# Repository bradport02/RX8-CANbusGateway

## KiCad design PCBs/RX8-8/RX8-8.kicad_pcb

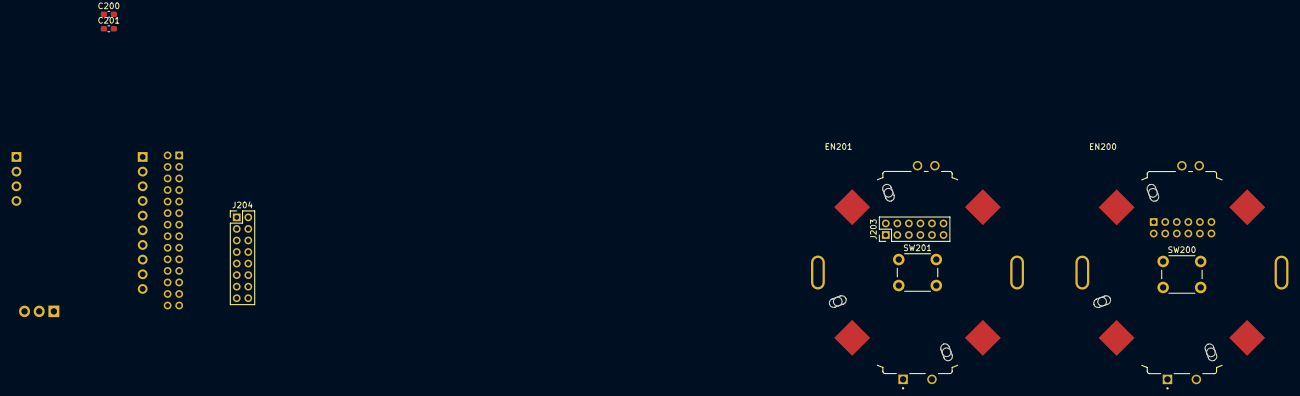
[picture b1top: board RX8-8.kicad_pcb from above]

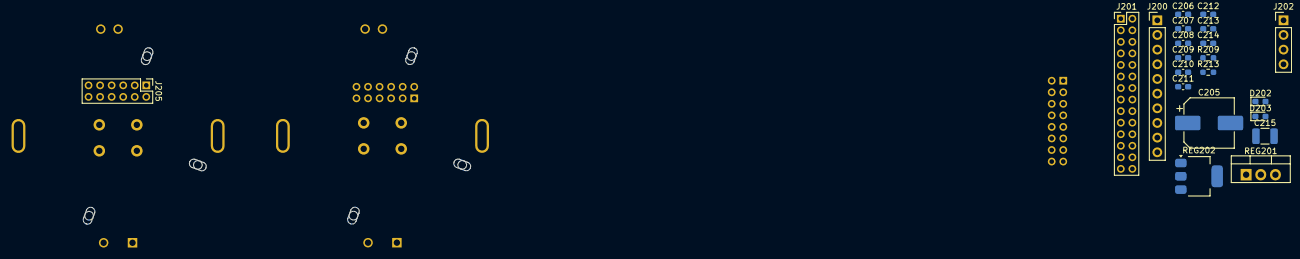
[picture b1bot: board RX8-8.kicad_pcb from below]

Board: 2 copper layers, 29 parts (21 on the bottom side), 30 nets, no tracks yet.

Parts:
C200, C201, C206, C207, C209, C211, C212, C213: 10n; C_0603_1608Metric_Pad1.08x0.95mm_HandSolder
C205: 47u; CP_Elec_8x10.5
C208, C210, C214: 100n; C_0603_1608Metric_Pad1.08x0.95mm_HandSolder
C215: 10u; C_1210_3225Metric_Pad1.33x2.70mm_HandSolder
D202, D203: LED; LED_0603_1608Metric_Pad1.05x0.95mm_HandSolder
EN200, EN201: PER351-P115-N0010; XDCR_PER351-P115-N0010
J200: OUT_TO_CCU; PinHeader_1x10_P2.54mm_Vertical
J201: Conn_01x24_Pin; PinHeader_2x14_P2.00mm_Vertical
J202: IND; PinHeader_1x04_P2.54mm_Vertical
J203, J205: GC9A01; PinHeader_2x06_P2.00mm_Vertical
J204: GC9A01; PinHeader_2x08_P2.00mm_Vertical
R209: 2K2; R_0603_1608Metric_Pad0.98x0.95mm_HandSolder
R213: 22k; R_0603_1608Metric_Pad0.98x0.95mm_HandSolder
REG201: LM7805_TO220; TO-220-3_Vertical
REG202: LD1117S33TR_SOT223; SOT-223-3_TabPin2
SW200, SW201: SW_Push; SW_PUSH_6mm_H4.3mm

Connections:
+12V: C205.1, C208.1, J201.1, REG201.1 (VI)
/Power and IO/CS1: J201.19, J203.8
/Power and IO/CS2: J201.22, J204.6
/Power and IO/CS3: J201.21, J205.8
/Power and IO/EN1A: C206.1, EN200.A, J201.5
/Power and IO/EN1B: C207.1, EN200.B, J201.6
/Power and IO/EN1C: C209.1, EN200.C, J201.7
/Power and IO/EN2A: C211.1, EN201.A, J201.8
/Power and IO/EN2B: C212.1, EN201.B, J201.9
/Power and IO/EN2C: C213.1, EN201.C, J201.10
/Power and IO/LCD_BACK: J201.27, J202.4, J203.2, J204.2, J205.2
/Power and IO/LCD_DC: J201.23, J203.7, J204.5, J205.7
/Power and IO/LCD_RST1: J201.14, J203.11
/Power and IO/LCD_RST2: J201.15, J204.9
/Power and IO/LCD_RST3: J201.24, J205.11
/Power and IO/MOSI: J201.18, J203.10, J204.8, J205.10
/Power and IO/SCK: J203.9, J204.7, J205.9
/Power and IO/SCL: J201.4, J204.14
/Power and IO/SDA: J201.3, J204.15
/Power and IO/SW1: C200.1, J201.11, SW200.1
/Power and IO/SW2: C201.1, J201.12, SW201.1
/Power and IO/TP_INT: J201.17, J204.13
/Power and IO/TP_RST: J201.16, J204.12
GND: C200.2, C201.2, C205.2, C208.2, C210.2, C211.2, C212.2, C213.2, C214.2, C215.2, EN200.D, EN200.SH1 (SHIELD), EN200.SH2 (SHIELD), EN200.SH3 (SHIELD), EN200.SH4 (SHIELD), EN200.SH5 (SHIELD), EN200.SH6 (SHIELD), EN201.D, EN201.SH1 (SHIELD), EN201.SH2 (SHIELD), EN201.SH3 (SHIELD), EN201.SH4 (SHIELD), EN201.SH5 (SHIELD), EN201.SH6 (SHIELD), R209.1, R213.2, REG201.2 (GND), REG202.1 (GND), SW200.2, SW201.2
unnamed: C206.2, C207.2, C209.2
unnamed: D202.1 (K), R209.2
unnamed: D203.1 (K), R213.1
P3V3: C215.1, D203.2 (A), J205.4, REG202.2 (VO)
P5V: C210.1, C214.1, D202.2 (A), J203.4, J204.4, J204.10, REG201.3 (VO), REG202.3 (VI)
PGND: J201.2, J203.1, J203.5, J203.6, J203.12, J204.1, J204.11, J205.1, J205.5, J205.6, J205.12

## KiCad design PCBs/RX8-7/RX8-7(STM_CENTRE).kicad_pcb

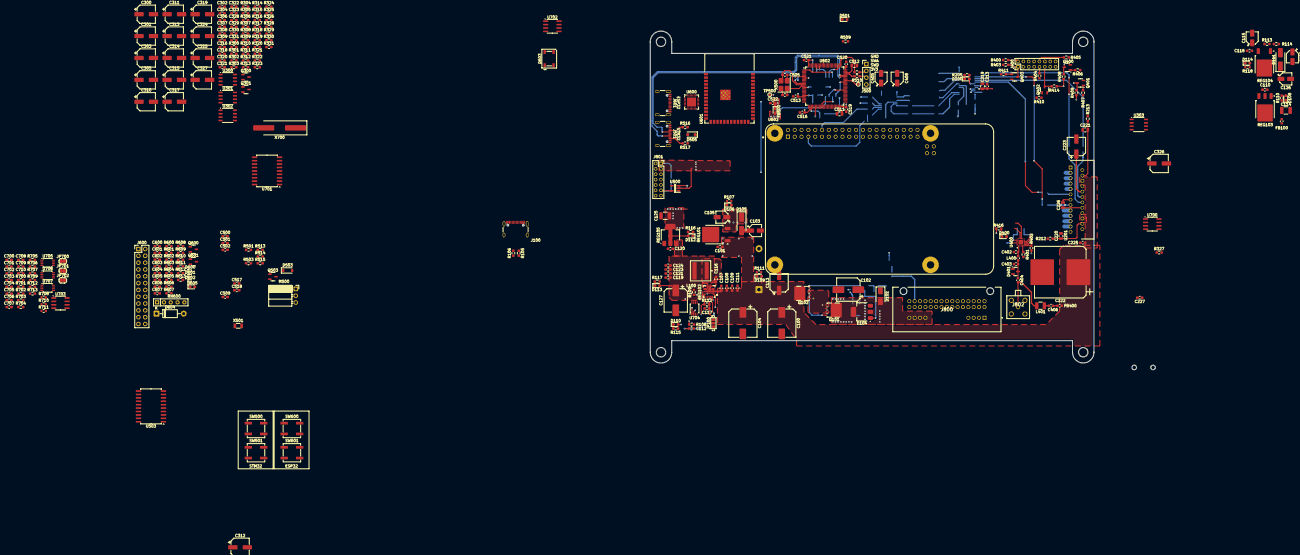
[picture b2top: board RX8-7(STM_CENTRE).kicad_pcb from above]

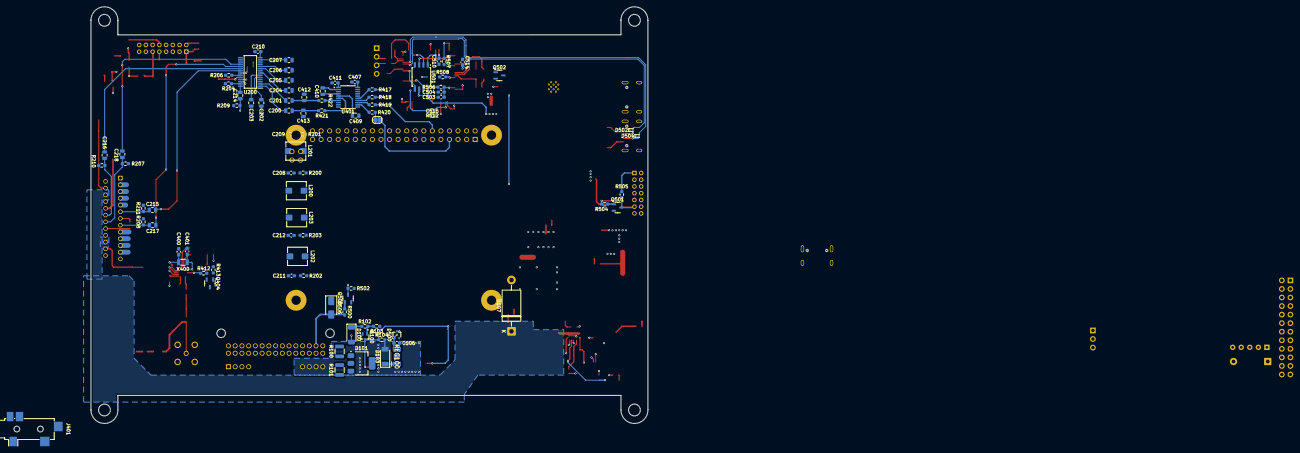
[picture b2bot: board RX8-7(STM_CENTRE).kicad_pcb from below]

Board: 4 copper layers, 165.3 x 123.7 mm, 387 parts (88 on the bottom side), 302 nets.

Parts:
C100: 100u; CP_Elec_10x10
C101, C106, C109, C110, C111, C116, C118, C120, C208, C209, C211, C212, C213, C225, C227, C328, C329, C330, C331, C407, C411, C500, C501, C502, C503, C509, C510, C513, C514, C515, C516, C519, C520, C521, C601, C602, C604, C605, C606, C700, C703, C704, C705, C706, C707, C708, C709, C710: 100n; C_0603_1608Metric_Pad1.08x0.95mm_HandSolder
C102: 10u; CP_Elec_8x10.5
C103, C115, C122, C405, C408: 10u; CP_Elec_4x5.4
C104: 220u; CP_Elec_10x10
C105: 1u; CP_Elec_4x5.7
C107, C108, C504, C522, C607: 10u; C_0603_1608Metric_Pad1.08x0.95mm_HandSolder
C112: 22n; C_0603_1608Metric_Pad1.08x0.95mm_HandSolder
C113, C223: 47u; CP_Elec_6.3x5.9
C114, C125: 10u; C_1210_3225Metric_Pad1.33x2.70mm_HandSolder
C117: 4.7u; C_0603_1608Metric_Pad1.08x0.95mm_HandSolder
C119, C121: 47u; C_0603_1608Metric_Pad1.08x0.95mm_HandSolder
C123: 22u; C_0603_1608Metric_Pad1.08x0.95mm_HandSolder
C124: 22uF; C_0603_1608Metric_Pad1.08x0.95mm_HandSolder
C126: 1u; CP_Elec_4x5.4
C127: 470u; CP_Elec_8x10.5
C200, C201, C202, C203, C204, C205, C206, C207, C214, C220, C221: 1u; C_0805_2012Metric
C210: 470n; C_0603_1608Metric_Pad1.08x0.95mm_HandSolder
C215, C216, C217, C218, C409, C410, C412, C413, C511, C512: 2u2; C_0805_2012Metric
C219: 10u; C_0805_2012Metric
C222: 4700u; CP_Elec_18x22
C226: 470n; C_0805_2012Metric
C300, C301, C303, C305, C314, C315, C317, C319: 10u; CP_Elec_6.3x7.7
C302, C304, C316, C318, C600, C603: 1u; C_0603_1608Metric_Pad1.08x0.95mm_HandSolder
C306, C307, C308, C309, C320, C321, C322, C323: 47p; C_0603_1608Metric_Pad1.08x0.95mm_HandSolder
C310, C311, C312, C313, C324, C325, C326, C327: 220u; CP_Elec_6.3x7.7
C400, C401, C701, C702: 22p; C_0603_1608Metric_Pad1.08x0.95mm_HandSolder
C402, C403: NA; C_0603_1608Metric
C404: 470p; C_0603_1608Metric
C406: 10u; C_0603_1608Metric
C505, C508: 12p; C_0603_1608Metric_Pad1.08x0.95mm_HandSolder
C517, C518: 15p; C_0603_1608Metric_Pad1.08x0.95mm_HandSolder
D100, D103: 1N5402; D_SOD-128
D101, D104: D_Zener; SOT-223-3_TabPin2
D102, D506: SMAJ24A; D_SMA
D105, D111: 1N4007; D_SMA_Handsoldering
D106, D108, D109, D110, D112, D113, D114, D200, D400, D501, D605: LED; LED_0603_1608Metric_Pad1.05x0.95mm_HandSolder
D107: 1.5KExxA; D_DO-201AE_P15.24mm_Horizontal
D401: NUP2105L; SOT-23
D500: BAT54W; SOT-323_SC-70
D502, D504, D600, D601, D602: ESD9B5.0ST5G; D_SOD-923
D503: 1N4001; D_SOD-123
D505: 1N5819; D_SOD-123F
D603: WS2812B; LED_WS2812B_PLCC4_5.0x5.0mm_P3.2mm
D604: 1N5819; D_DO-41_SOD81_P10.16mm_Horizontal
FB100, FB400: FerriteBead; C_0603_1608Metric
FB500: FerriteBead; LED_0603_1608Metric_Pad1.05x0.95mm_HandSolder
J100, J501, J601: USB_C_Receptacle_USB2.0_16P; USB_C_Receptacle_GCT_USB4105-xx-A_16P_TopMnt_Horizontal
J400: Conn_01x15_Pin; PinHeader_2x08_P2.00mm_Vertical
J401: AudioJack3_Ground; Jack_3.5mm_CUI_SJ2-3593D-SMT_Horizontal
J500: Conn_01x04_Pin; PinHeader_1x04_P2.54mm_Vertical
J600: Conn_01x24_Pin; PinHeader_2x12_P2.54mm_Vertical
J800: 34958-0383; 349580383
J801: Conn_01x12_Pin; PinSocket_2x07_P2.00mm_Vertical
J802: 59S10H-400T5-A; 59S10H400T5A
JP100: Jumper_3_Bridged12; SolderJumper-3_P1.3mm_Open_Pad1.0x1.5mm_NumberLabels
JP600: Jumper_2_Open; SolderJumper-2_P1.3mm_Open_RoundedPad1.0x1.5mm
JP700, JP701, JP702: Jumper_2_Bridged; SolderJumper-2_P1.3mm_Open_RoundedPad1.0x1.5mm
L100: 4.7uH; XAL7030472MEC
L200, L201, L202, L203: 10u; L_Bourns_SRP5030T
L400: NA; C_0603_1608Metric
L401: 10u; L_1210_3225Metric
M500: Fan_3pin; PinSocket_1x03_P2.54mm_Horizontal
Q100: NPN; SOT65P210X125-3N
Q101, Q102: SQJ407EP-T1_GE3; PowerPAK-SO-8L_Option-2_VIS
Q300, Q301: NPN; SOT-23-3
Q400, Q401, Q402, Q403, Q404, Q500, Q501, Q502, Q503, Q600, Q601: NPN; SOT-23-3(CORRECTED)
R100, R101: 10k; R_1210_3225Metric
R102, R110, R116, R205, R416, R613: 22k; R_0603_1608Metric_Pad0.98x0.95mm_HandSolder
R103, R104, R206, R207, R208, R210, R211, R213, R330, R331, R400, R401, R402, R403, R404, R405, R408, R409, R413, R414, R417, R418, R419, R420, R500, R501, R502, R503, R504, R505, R508, R509, R514, R600, R601, R609, R610, R702, R707, R709, R712, R713: 10k; R_0603_1608Metric_Pad0.98x0.95mm_HandSolder
R105, R106, R516, R517, R604, R605: 5k1; R_0603_1608Metric_Pad0.98x0.95mm_HandSolder
R107, R111, R118: 22k; R_0603_1608Metric
R108: 62k; R_0603_1608Metric_Pad0.98x0.95mm_HandSolder
R109: 51k; R_0603_1608Metric_Pad0.98x0.95mm_HandSolder
R112, R204, R209: 100k; R_0603_1608Metric_Pad0.98x0.95mm_HandSolder
R113: 240R; R_0603_1608Metric_Pad0.98x0.95mm_HandSolder
R114: 1k5; R_0603_1608Metric_Pad0.98x0.95mm_HandSolder
R115, R117: 2K2; R_0603_1608Metric_Pad0.98x0.95mm_HandSolder
R200, R201, R202, R203: 10R; R_0603_1608Metric_Pad0.98x0.95mm_HandSolder
R212, R603: 47k; R_0603_1608Metric_Pad0.98x0.95mm_HandSolder
R300, R301, R314, R315: 27k; R_0603_1608Metric_Pad0.98x0.95mm_HandSolder
R302, R303, R304, R305, R312, R313, R316, R317, R318, R319, R326, R327: 4K7; R_0603_1608Metric_Pad0.98x0.95mm_HandSolder
R306, R307, R320, R321: 1K; R_0603_1608Metric_Pad0.98x0.95mm_HandSolder
R308, R309, R310, R311, R322, R323, R324, R325: 4R7; R_0603_1608Metric_Pad0.98x0.95mm_HandSolder
R328, R329, R406, R407, R410, R411, R412, R512, R515, R608: 1k; R_0603_1608Metric_Pad0.98x0.95mm_HandSolder
R421, R422: 470R; R_0603_1608Metric_Pad0.98x0.95mm_HandSolder
R506, R507, R606, R607, R611, R612, R700, R703, R704: 0R; R_0603_1608Metric_Pad0.98x0.95mm_HandSolder
R510, R511: 22R; R_0603_1608Metric_Pad0.98x0.95mm_HandSolder
R513: 82k; R_0603_1608Metric_Pad0.98x0.95mm_HandSolder
R602: 22k1; R_0603_1608Metric_Pad0.98x0.95mm_HandSolder
R701, R705, R706: 120R; R_0603_1608Metric_Pad0.98x0.95mm_HandSolder
R708, R710, R711: 10k; R_0603_1608Metric
REG100: TPS7B8233QDGNRQ1; SOP65P490X110-9N
REG101: LF80_TO252; TO-252-2
REG102: MPQ4317GRE-5-AEC1-P; QFN-20_MPQ4317_MNP
REG103: NCV1117DT33T5G; TO-252-3_TabPin2
REG104: NCV317MBDTRKG; TO-252-2
REG105: LD1117S33TR_SOT223; SOT-223-3_TabPin2
RN600: R_Network04; R_Array_SIP5
SW500, SW501, SW600, SW601: SW_Push; SW_SPST_B3SL-1002P
TP500, TP501: TestPoint; TestPoint_Pad_D1.0mm
U200: TDA7719; SOP65P640X120-28N
U201: TDA7388; TO100P465X2910X1977-25P
U300, U301, U302, U303: NJM4556A; SSOP-8_3.9x5.05mm_P1.27mm
U400: SI4703-C19-GM; SI4703C19GM
U401: PCM5102A; TSSOP-20_4.4x6.5mm_P0.65mm
U500: MCP1402T-E_OT; SOT95P270X145-5N
U501: W25Q32JVSS; SOIC-8_5.3x5.3mm_P1.27mm
U502: STM32H750VBTx; LQFP-100_14x14mm_P0.5mm
U503: 74HC245; SOIC-20W_7.5x12.8mm_P1.27mm
U600: CP2102N-Axx-xQFN28; QFN-28-1EP_5x5mm_P0.5mm_EP3.35x3.35mm
U601: ESP32-S3-WROOM-1
U602: Raspberry_Pi_5; MODULE_RASPBERRY_PI_4B_4GB
U700, U702, U703: MCP2551-I-SN; SOIC-8_3.9x4.9mm_P1.27mm
U701: MCP2515-xSO; SOIC-18W_7.5x11.6mm_P1.27mm
U704, U705, U706, U707: LM75B; TSSOP-8_3x3mm_P0.65mm
X400, X501: 32.768K; Crystal_SMD_3215-2Pin_3.2x1.5mm
X500: 25MHz; Crystal_SMD_3225-4Pin_3.2x2.5mm_HandSoldering
X700: 8MHz; Crystal_SMD_HC49-SD_HandSoldering

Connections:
3P3: C408.1, C411.1, D400.2 (A), FB100.1, R402.2, R413.2, U400.10 (VIO), U400.11 (VD), U400.16 (VA), U401.1 (CPVDD), U401.8 (AVDD)
8P5: C110.1, C126.1, C213.1, C219.1, C328.2, C329.2, C330.2, C331.2, D111.1 (K), D114.2 (A), R113.1, REG103.3 (VI), REG104.2 (VOUT), U200.24 (VDD), U300.8 (V+), U301.8 (V+), U302.8 (V+), U303.8 (V+)
+12V: C100.1, C101.1, C104.1, C107.1, C108.1, C109.1, C111.1, C113.1, C115.1, C118.1, C222.1, C225.1, D107.1 (A1), D109.2 (A), D503.1 (K), FB400.1, J400.3, J400.4, J600.1, J600.2, M500.2 (+), Q102.5 (D), R330.2, R331.2, R408.2, R409.2, R414.2, REG101.1 (VI), REG102.3 (VIN), REG102.12 (VIN), REG104.3 (VIN), U201.6 (VCC_1), U201.20 (VCC_2)
+BAT: D102.2 (A2), D103.2 (A), D104.2 (A), J800.5, J800.6, J800.7, J800.8, Q101.5 (D), R104.2
/AMPENABLE: J800.28, Q300.1 (C), R330.1
/ANT_IN: C404.2, J802.1, L401.1
/Audio2/APSTATE: R329.1, U601.18 (IO10)
/Audio3/CDBUS+: R411.1, U601.17 (IO9)
/Audio3/CDEJECT: R410.1, U601.12 (IO8)
/Audio3/CDMUTE: R406.1, U601.6 (IO6)
/Audio3/CD_ENABLE: R407.1, U601.7 (IO7)
/Audio3/FMGPIO1: R412.1, U400.19 (GPIO1)
/Audio3/I2S_BCLK: R419.1, U602.12 (GPIO18/SPI1_~CE0/PCM_CLK/PWM0)
/Audio3/I2S_DOUT: R418.1, U602.40 (GPIO21/SPI1_SCLK/PCM_DOUT)
/Audio3/I2S_LRCLK: R417.1, U602.35 (GPIO19/SPI1_MISO/PCM_FS)
/Audio3/I2S_SCLK: JP600.2 (B), R420.1
/Audio3/MediaBUS+: J400.1, Q403.1 (C), R403.1
/Audio3/MediaBUS-: J400.2, R400.2
/Audio3/MediaCLK: J400.9, R404.1
/Audio3/MediaDO: J400.10, R405.1
/Audio3/MediaEJECT: J400.7, Q401.1 (C), R409.1
/Audio3/MediaENABLE: J400.11, Q402.1 (C), R414.1
/Audio3/MediaMUTE: J400.12, Q400.1 (C), R408.1
/Audio3/RF_IN: C402.2, L400.1, U400.2 (FMIP)
/Audio3/Tuner_RST: R401.2, U400.5 (~RST), U601.4 (IO4)
/Audio/AMP_MUTE: R206.2, R212.1, U601.20 (IO12)
/Audio/AUXIN_L: C206.1, J401.T
/Audio/AUXIN_R: C207.1, J401.R
/Audio/BEEP_OUT: C214.2, R209.1, R512.2
/Audio/CDIN_L: C202.1, J400.15
/Audio/CDIN_R: C203.1, J400.13
/Audio/DAC_OUTL: C200.1, C413.2, R421.2
/Audio/DAC_OUTR: C201.1, C412.2, R422.2
/Audio/FMOUT_L: C204.1, U400.14 (LOUT)
/Audio/FMOUT_R: C205.1, U400.13 (ROUT)
/Audio/IN1: C215.2, C301.2, R211.1, U201.11 (IN1)
/Audio/IN2: C216.2, C300.2, R210.1, U201.12 (IN2)
/Audio/IN3: C217.2, C315.2, R208.1, U201.15 (IN3)
/Audio/IN4: C218.2, C314.2, R207.1, U201.14 (IN4)
/Audio/LMOUT: R204.2, U502.30 (PA6)
/Audio/OUT1+: C312.1, L200.1, U201.9 (OUT1+)
/Audio/OUT1-: C208.2, C313.1, J800.27, U201.7 (OUT1-)
/Audio/OUT2+: C310.1, L201.1, U201.5 (OUT2+)
/Audio/OUT2-: C209.2, C311.1, J800.12, U201.3 (OUT2-)
/Audio/OUT3+: C326.1, L203.1, U201.17 (OUT3+)
/Audio/OUT3-: C212.2, C327.1, J800.10, U201.19 (OUT3-)
/Audio/OUT4+: C324.1, L202.1, U201.21 (OUT4+)
/Audio/OUT4-: C211.2, C325.1, J800.25, U201.23 (OUT4-)
/Audio/OUT_FL+: J800.26, L200.2, R200.1
/Audio/OUT_FR+: J800.24, L202.2, R202.1
/Audio/OUT_RL+: J800.11, L201.2, R201.1
/Audio/OUT_RR+: J800.9, L203.2, R203.1
/AudioPilot: J800.13, Q301.1 (C), R331.1
/CAN1H: J800.20, JP700.1 (A), U700.7 (CANH)
/CAN1L: J800.21, R701.1, U700.6 (CANL)
/CAN2H: J800.22, R705.1, R706.1, U702.7 (CANH), U703.7 (CANH)
/CAN2L: J800.23, JP701.1 (A), JP702.1 (A), U702.6 (CANL), U703.6 (CANL)
/Connectors/Illumination+: D506.2 (A2), J800.37, R500.1
/Connectors/LCD_AC: J801.4, U503.15 (B3)
/Connectors/LCD_BACKLIGHT: J801.11, Q501.1 (C), R505.1, U500.5 (OUT)
/Connectors/LCD_CS: J801.5, U503.18 (B0)
/Connectors/LCD_EN: J801.9, U503.13 (B5)
/Connectors/LCD_MOSI: J801.7, U503.16 (B2)
/Connectors/LCD_RS: J801.3, U503.14 (B4)
/Connectors/LCD_SCK: J801.6, U503.17 (B1)
/LED_DOUT: D603.2 (DOUT), J800.32
/MCU1/BOOT0: C501.1, C510.2, R501.2, SW501.2, U502.94 (BOOT0)
/MCU1/Backlight_PWM: R504.1, U500.3 (IN), U502.89 (PB3)
/MCU1/CAN1_RXD: U502.81 (PD0), U700.4 (RXD)
/MCU1/CAN1_TXD: U502.82 (PD1), U700.1 (TXD)
/MCU1/CAN2_RXD: U502.52 (PB13), U703.4 (RXD)
/MCU1/CAN2_TXD: U502.51 (PB12), U703.1 (TXD)
/MCU1/CCU_RX: J600.4, U503.11 (B7)
/MCU1/CCU_TX: J600.3, U503.12 (B6)
/MCU1/ESP32_RX: U502.22 (PA0), U601.10 (IO17)
/MCU1/ESP32_TX: U502.23 (PA1), U601.11 (IO18)
/MCU1/FAN_TACHO: R513.2, R514.1, U502.59 (PD12)
/MCU1/Illum_IN: Q500.1 (C), R502.1, U502.31 (PA7)
/MCU1/MT1_UH: J600.7, U502.39 (PE9)
/MCU1/MT1_UL: J600.8, U502.38 (PE8)
/MCU1/MT1_VH: J600.9, U502.41 (PE11)
/MCU1/MT1_VL: J600.10, U502.40 (PE10)
/MCU1/MT1_WH: J600.11, U502.43 (PE13)
/MCU1/MT1_WL: J600.12, U502.42 (PE12)
/MCU1/MT2_UH: J600.13, U502.63 (PC6)
/MCU1/MT2_UL: J600.14, U502.29 (PA5)
/MCU1/MT2_VH: J600.15, U502.64 (PC7)
/MCU1/MT2_VL: J600.16, U502.34 (PB0)
/MCU1/MT2_WH: J600.17, U502.65 (PC8)
/MCU1/MT2_WL: J600.18, U502.35 (PB1)
/MCU1/NRST: R503.2, R508.2, U502.14 (NRST)
/MCU1/OUT1Hz: Q502.2 (B), TP500.1, U502.7 (PC13)
/MCU1/OUT25MHz: TP501.1, U502.67 (PA8)
/MCU1/QSPI_CLK: U501.6 (CLK), U502.36 (PB2)
/MCU1/QSPI_CS: U501.1 (~CS), U502.92 (PB6)
/MCU1/QSPI_D0: U501.5 (DI/IO_{0}), U502.66 (PC9)
/MCU1/QSPI_D1: U501.2 (DO/IO_{1}), U502.78 (PC10)
/MCU1/QSPI_D2: U501.3 (~WP/IO_{2}), U502.1 (PE2)
/MCU1/QSPI_D3: U501.7 (~HOLD/~RESET/IO_{3}), U502.60 (PD13)
/MCU1/STM32_RX: U502.83 (PD2), U602.8 (GPIO14/UART_TXD)
/MCU1/STM32_TX: U502.80 (PC12), U602.10 (GPIO15/UART_RXD)
/MCU1/U1LCD_CS: U502.15 (PC0), U503.2 (A0)
/MCU1/U1LCD_MOSI: U502.16 (PC1), U503.4 (A2)
/MCU1/U1LCD_SCK: U502.46 (PB10), U503.3 (A1)
/MCU1/UART7_RX: U502.37 (PE7), U503.9 (A7)
/MCU1/UART7_TX: U502.77 (PA15), U503.8 (A6)
/MCU1/USB_CC1: J501.A5 (CC1), R516.1
/MCU1/USB_CC2: J501.B5 (CC2), R517.1
/MCU1/USB_DN: D502.2 (A2), J501.A7 (D-), J501.B7 (D-), U502.70 (PA11)
/MCU1/USB_DP: D504.2 (A2), J501.A6 (D+), J501.B6 (D+), U502.71 (PA12)
/MCU2/CS1: J600.21, U601.32 (IO39)
/MCU2/CS2: J600.22, U601.33 (IO40)
/MCU2/CS3: J600.23, U601.9 (IO16)
/MCU2/LED_DOUT: D603.4 (DIN), U601.5 (IO5), U601.8 (IO15)
/MCU2/PI_CS: U602.24 (~CE0_SPI0/GPIO08), U701.16 (~CS)
/MCU2/PI_INT: U602.22 (GPIO25/SDIO_DAT1), U701.12 (~INT)
/MCU2/PI_MISO: U602.21 (MISO_SPI0/GPIO09), U701.15 (SO)
/MCU2/PI_MOSI: U602.19 (MOSI_SPI0/GPIO10), U701.14 (SI)
/MCU2/PI_SCLK: U602.23 (SCLK_SPI0/GPIO11), U701.13 (SCK)
/MCU2/Pi_SCL: RN600.4 (R3), U602.28 (ID_SC_I2C0/GPIO01)
/MCU2/Pi_SDA: RN600.5 (R4), U602.27 (ID_SD_I2C0/GPIO00)
/MCU2/U6DTR: Q601.3 (E), R600.1, U600.28 (~DTR)
/MCU2/U6RTS: Q600.3 (E), R601.1, U600.24 (~RTS)
/MCU2/U6RXD: R611.2, U601.36 (RXD0)
/MCU2/U6TXD: R612.2, U601.37 (TXD0)
/MCU2/U6_EN: C601.2, C603.1, R606.2, R609.2, SW600.2, U601.3 (EN)
/MCU2/U6_GPIO0: C602.2, R607.1, SW601.2, U601.27 (IO0)
/MCU2/U6_MISO: J600.24, U601.34 (IO41)
/MCU2/USB2_CC1: J601.A5 (CC1), R604.1
/MCU2/USB2_CC2: J601.B5 (CC2), R605.1
/MCU2/USB2_D+: D602.2 (A2), J601.A6 (D+), J601.B6 (D+), U600.4 (D+)
/MCU2/USB2_D-: D601.2 (A2), J601.A7 (D-), J601.B7 (D-), U600.5 (D-)
/Power/ENABLE: D100.2 (A), D101.1 (K), R100.2, R101.2, REG102.9 (EN)
/Power/PG_OUT: D110.2 (A), R112.1, REG102.14 (PG)
/SCL: J600.5, RN600.3 (R2), U200.26 (SDA), U400.8 (SDIO), U502.96 (PB9), U601.39 (IO1), U704.2 (SCL), U705.2 (SCL), U706.2 (SCL), U707.2 (SCL)
/SDA: J600.6, RN600.2 (R1), U200.25 (SCL), U400.7 (SCLK), U502.95 (PB8), U601.38 (IO2), U704.1 (SDA), U705.1 (SDA), U706.1 (SDA), U707.1 (SDA)
/Sensors/T_SD: R707.1, R708.1, R710.1, R711.1, U704.3 (O.S.), U705.3 (O.S.), U706.3 (O.S.), U707.3 (O.S.)
ACC: J800.38, R100.1
AGND: C100.2, C101.2, C102.2, C103.2, C104.2, C105.2, C106.2, C107.2, C108.2, C109.2, C110.2, C111.2, C112.2, C113.2, C114.2, C115.2, C117.2, C118.2, C119.2, C120.2, C121.2, C122.2, C123.2, C124.2, C125.2, C126.2, C127.2, C210.2, C213.2, C219.2, C220.2, C221.2, C222.2, C223.2, C225.2, C226.2, C227.2, C302.1, C304.1, C316.1, C318.1, C328.1, C329.1, C330.1, C331.1, C400.2, C401.2, C402.1, C403.1, C405.2, C407.2, C408.2, C409.1, C411.2, C412.1, C413.1, C500.2, C501.2, C502.2, C503.2, C504.2, C505.1, C508.2, C509.1, C510.1, C511.2, C512.2, C513.1, C514.1, C515.1, C516.1, C517.2, C518.2, C519.1, C520.1, C521.1, C522.2, C600.2, C601.1, C602.1, C603.2, C604.2, C605.2, C606.2, C607.2, C700.1, C701.1, C702.1, C703.1, C704.1, C705.1, C706.1, C707.1, C708.1, C709.1, C710.1, D101.2 (A), D102.1 (A1), D107.2 (A2), D401.1 (A1), D502.1 (A1), D504.1 (A1), D506.1 (A1), D600.1 (A1), D601.1 (A1), D602.1 (A1), D603.3 (VSS), J100.A1 (GND), J100.A12 (GND), J100.B1 (GND), J100.B12 (GND), J100.S1 (SHIELD), J400.5, J400.6, J400.14, J401.S, J500.1, J501.A1 (GND), J501.A12 (GND), J501.B1 (GND), J501.B12 (GND), J501.S1 (SHIELD), J601.A1 (GND), J601.A12 (GND), J601.B1 (GND), J601.B12 (GND), J601.S1 (SHIELD), J800.1, J800.2, J800.3, J800.4, J801.8, J801.10, J801.12, J802.2, J802.3, J802.4, J802.5, JP100.1 (A), Q100.3 (E), Q300.3 (E), Q301.3 (E), Q400.3 (E), Q401.3 (E), Q402.3 (E), Q403.3 (E), Q404.3 (E), Q500.3 (E), Q501.3 (E), Q502.3 (E), Q503.3 (E), R101.1, R103.1, R105.2, R106.2, R107.1, R108.2, R109.2, R110.2, R111.1, R114.2, R115.1, R116.2, R117.1, R118.1, R205.2, R207.2, R208.2, R209.2, R210.2, R211.2, R400.1, R401.1, R507.1, R508.1, R514.2, R516.2, R517.2, R603.1, R604.2, R605.2, R610.2, R613.1, R700.2, R703.2, R704.2, REG100.4 (GND), REG100.5 (GND), REG100.6 (GND), REG100.9 (EP), REG101.2 (GND), REG102.4 (PGND), REG102.5 (PGND), REG102.10 (PGND), REG102.11 (PGND), REG102.17 (AGND), REG103.1 (GND), REG105.1 (GND), SW501.1, SW600.1, SW601.1, U200.3 (QD1G), U200.4 (QD2G), U200.8 (QD3G), U200.11 (FDL-/QD4G), U200.12 (FDR+/QD4G), U200.15 (GND), U201.1 (TAB), U201.2 (P-GND2), U201.8 (P-GND1), U201.13 (S-GND), U201.18 (P-GND3), U201.24 (P-GND4), U300.4 (V-), U301.4 (V-), U302.4 (V-), U303.4 (V-), U400.3 (RFGND), U400.4 (GND), U400.12 (GND), U400.15 (GND), U400.21 (GND), U401.3 (CPGND), U401.9 (AGND), U401.10 (DEMP), U401.11 (FLT), U401.16 (FMT), U401.17 (XSMT), U401.19 (DGND), U500.1 (GND_1), U500.4 (GND_2), U501.4 (GND), U502.10 (VSS), U502.19 (VSSA), U502.26 (VSS), U502.49 (VSS), U502.74 (VSS), U502.99 (VSS), U503.10 (GND), U600.3 (GND), U600.29 (GND), U601.1 (GND), U601.40 (GND), U601.41 (GND), U602.6 (GND), U602.9 (GND), U602.14 (GND), U602.20 (GND), U602.25 (GND), U602.30 (GND), U602.34 (GND), U602.39 (GND), U700.2 (VSS), U701.9 (VSS), U702.2 (VSS), U703.2 (VSS), U704.4 (GND), U704.5 (A2), U704.6 (A1), U704.7 (A0), U705.4 (GND), U705.5 (A2), U705.6 (A1), U706.4 (GND), U706.5 (A2), U706.7 (A0), U707.4 (GND), U707.6 (A1), U707.7 (A0), X500.2, X500.4
AMPSTATE: R213.1, R328.1, U601.21 (IO13)
unnamed: C116.2, L100.1, REG102.7 (SW), REG102.8 (SW)
unnamed: C208.1, R200.2
unnamed: C209.1, R201.2
unnamed: C211.1, R202.2
unnamed: C212.1, R203.2
unnamed: C300.1, C303.2
unnamed: C301.1, C305.2
unnamed: C306.2, R309.2, U300.7
unnamed: C307.2, R311.2, U301.7
unnamed: C308.2, R308.2, U300.1
unnamed: C309.2, R310.2, U301.1
unnamed: C310.2, R306.2, R308.1, R312.2
unnamed: C311.2, R304.2, R309.1
unnamed: C312.2, R307.2, R310.1, R313.2
unnamed: C313.2, R305.2, R311.1
unnamed: C314.1, C317.2
unnamed: C315.1, C319.2
unnamed: C320.2, R323.2, U302.7
unnamed: C321.2, R325.2, U303.7
unnamed: C322.2, R322.2, U302.1
unnamed: C323.2, R324.2, U303.1
unnamed: C324.2, R320.2, R322.1, R326.2
unnamed: C325.2, R318.2, R323.1
unnamed: C326.2, R321.2, R324.1, R327.2
unnamed: C327.2, R319.2, R325.1
unnamed: C406.1, L401.2
unnamed: C406.2, FB400.2
unnamed: C500.1, SW500.1
unnamed: C502.1, R503.1, SW500.2
unnamed: C511.1, U502.48 (VCAP)
unnamed: C512.1, U502.73 (VCAP)
unnamed: D100.1 (K), R102.1
unnamed: C102.1, D103.1 (K), REG100.1 (IN), REG100.2 (EN)
unnamed: D104.1 (K), Q100.1 (C), Q101.4 (G), Q102.4 (G), R104.1
unnamed: C103.1, D105.2 (A)
unnamed: D106.1 (K), R107.2
unnamed: C114.1, D108.2 (A), FB100.2, REG103.2 (VO)
unnamed: D108.1 (K), R110.1
unnamed: D109.1 (K), R111.2
unnamed: D110.1 (K), R115.2
unnamed: C122.1, D111.2 (A), R113.2, R114.1, REG104.1 (ADJUST)
unnamed: D112.1 (K), R116.1
unnamed: D113.1 (K), R117.2
unnamed: D114.1 (K), R118.2
unnamed: D200.2 (A), U200.22 (WIN_TC_/_VREF)
unnamed: D200.1 (K), R205.1
unnamed: D400.1 (K), R416.1
unnamed: C403.2, C404.1, D401.2 (A2), L400.2
unnamed: D501.1 (K), R509.2
unnamed: D503.2 (A), M500.1 (-), Q503.1 (C)
unnamed: D605.2 (A), U602.2 (5V), U602.4 (5V)
unnamed: D605.1 (K), R613.2
unnamed: J100.A5 (CC1), R106.1
unnamed: J100.B5 (CC2), R105.1
unnamed: J500.2, R511.2
unnamed: J500.3, R510.2
unnamed: C117.1, JP100.3 (B), R112.2, REG102.16 (VCC)
unnamed: JP100.2 (C), REG102.1 (MODE)
unnamed: JP600.1 (A), U602.7 (GPCLK0/GPIO04)
unnamed: JP700.2 (B), R701.2
unnamed: JP701.2 (B), R705.2
unnamed: JP702.2 (B), R706.2
unnamed: M500.3 (Tacho), R513.1
unnamed: Q100.2 (B), R102.2, R103.2
unnamed: Q101.1 (S), Q101.2 (S), Q101.3 (S), Q102.1 (S), Q102.2 (S), Q102.3 (S)
unnamed: Q300.2 (B), R328.2
unnamed: Q301.2 (B), R329.2
unnamed: Q400.2 (B), R406.2
unnamed: Q401.2 (B), R407.2
unnamed: Q402.2 (B), R410.2
unnamed: Q403.2 (B), R411.2
unnamed: Q404.2 (B), R412.2
unnamed: Q404.1 (C), R413.1, R416.2
unnamed: Q500.2 (B), R500.2
unnamed: Q501.2 (B), R504.2
unnamed: Q502.1 (C), R509.1
unnamed: Q503.2 (B), R515.2
unnamed: Q600.2 (B), R600.2
unnamed: Q600.1 (C), R606.1
unnamed: Q601.2 (B), R601.2
unnamed: Q601.1 (C), R607.2
unnamed: C116.1, REG102.6 (BST)
unnamed: R108.1, REG102.20 (FREQ)
unnamed: C112.1, REG102.19 (SS)
unnamed: R109.1, REG102.2 (SYNCIN)
unnamed: C210.1, U200.14 (CREF)
unnamed: R204.1, U200.27 (DC_ERR_/_MOUT)
unnamed: C206.2, U200.10 (FDL+/QD4L)
unnamed: C207.2, U200.13 (FDR+/QDAR)
unnamed: R206.1, U200.23 (MUTE)
unnamed: C215.1, U200.21 (OUTLF)
unnamed: C216.1, U200.20 (OUTLR)
unnamed: C218.1, U200.18 (OUTRF)
unnamed: C217.1, U200.19 (OUTRR)
unnamed: C200.2, U200.1 (QD1L)
unnamed: C201.2, U200.2 (QD1R)
unnamed: C202.2, U200.5 (QD2L)
unnamed: C203.2, U200.6 (QD2R)
unnamed: C204.2, U200.7 (QD3L)
unnamed: C205.2, U200.9 (QD3R)
unnamed: C214.1, U200.28 (WIN_IN_/_BEEP)
unnamed: C226.1, C227.1, U201.16 (AC-GND)
unnamed: C220.1, R212.2, U201.22 (MUTE)
unnamed: C221.1, R213.2, U201.4 (ST-BY)
unnamed: C223.1, U201.10 (SVR)
unnamed: C302.2, C303.1, R300.1, U300.3 (+)
unnamed: C308.1, R302.2, R306.1, U300.2 (-)
unnamed: R300.2, R301.2, R302.1, R303.1, R314.2, R315.2, R316.1, R317.1, U300.5 (+), U301.5 (+), U302.5 (+), U303.5 (+)
unnamed: C306.1, R304.1, R312.1, U300.6 (-)
unnamed: C304.2, C305.1, R301.1, U301.3 (+)
unnamed: C309.1, R303.2, R307.1, U301.2 (-)
unnamed: C307.1, R305.1, R313.1, U301.6 (-)
unnamed: C316.2, C317.1, R314.1, U302.3 (+)
unnamed: C322.1, R316.2, R320.1, U302.2 (-)
unnamed: C320.1, R318.1, R326.1, U302.6 (-)
unnamed: C318.2, C319.1, R315.1, U303.3 (+)
unnamed: C323.1, R317.2, R321.1, U303.2 (-)
unnamed: C321.1, R319.1, R327.1, U303.6 (-)
unnamed: C401.1, U400.17 (GPIO3), X400.2
unnamed: C400.1, U400.9 (RCLK), X400.1
unnamed: R402.1, U400.6 (~SEN)
unnamed: R419.2, U401.13 (BCK)
unnamed: C410.1, U401.4 (CAPM)
unnamed: C410.2, U401.2 (CAPP)
unnamed: R418.2, U401.14 (DIN)
unnamed: R417.2, U401.15 (LRCK)
unnamed: R421.1, U401.6 (OUTL)
unnamed: R422.1, U401.7 (OUTR)
unnamed: R420.2, U401.12 (SCK)
unnamed: C409.2, U401.5 (VNEG)
unnamed: C515.2, R512.1, U502.28 (PA4)
unnamed: R510.1, U502.72 (PA13)
unnamed: R511.1, U502.76 (PA14)
unnamed: R515.1, U502.53 (PB14)
unnamed: C517.1, U502.8 (PC14), X501.1
unnamed: C518.1, U502.9 (PC15), X501.2
unnamed: C505.2, U502.12 (PH0), X500.3
unnamed: C508.1, U502.13 (PH1), X500.1
unnamed: C513.2, C514.2, C516.2, C519.2, C520.2, C521.2, C522.1, FB500.1, R506.2, R507.2, U502.11 (VDD), U502.21 (VDDA), U502.27 (VDD), U502.50 (VDD), U502.75 (VDD), U502.100 (VDD)
unnamed: C503.1, C504.1, R506.1, U502.20 (VREF+)
unnamed: R612.1, U600.25 (RXD)
unnamed: R611.1, U600.26 (TXD)
unnamed: C600.1, R602.2, R603.2, U600.8 (VBUS)
unnamed: R608.1, U600.9 (~RST)
unnamed: R610.1, U600.11 (~SUSPEND)
unnamed: R700.1, U700.8 (Rs)
unnamed: C702.2, U701.8 (OSC1), X700.1
unnamed: C701.2, U701.7 (OSC2), X700.2
unnamed: U701.2 (RXCAN), U702.4 (RXD)
unnamed: U701.1 (TXCAN), U702.1 (TXD)
unnamed: R702.1, U701.17 (~RESET)
unnamed: R703.1, U702.8 (Rs)
unnamed: R704.1, U703.8 (Rs)
unnamed: R709.2, U705.7 (A0)
unnamed: R712.2, U706.6 (A1)
unnamed: R713.2, U707.5 (A2)
P3V3: C125.1, C405.1, C407.1, C509.2, C604.1, C605.1, C607.1, C707.2, C708.2, C709.2, C710.2, D112.2 (A), D500.3 (K), D501.2 (A), FB500.2, J500.4, R501.1, R502.2, R608.2, R609.1, R707.2, R708.2, R709.1, R710.2, R711.2, R712.1, R713.1, REG105.2 (VO), RN600.1 (common), U401.20 (DVDD), U501.8 (VCC), U600.6 (VDD), U600.7 (VREGIN), U601.2 (3V3), U704.8 (+Vs), U705.8 (+Vs), U706.8 (+Vs), U707.8 (+Vs)
P5V: C119.1, C120.1, C121.1, C123.1, C124.1, C127.1, C606.1, C700.2, C703.2, C704.2, C705.2, C706.2, D113.2 (A), D505.1 (K), D603.1 (VDD), D604.1 (K), J100.A4 (VBUS), J100.A9 (VBUS), J100.B4 (VBUS), J100.B9 (VBUS), J801.2, L100.2, R403.2, R404.2, R405.2, R702.2, REG102.18 (FB), REG105.3 (VI), U503.1 (A->B), U503.19 (CE), U503.20 (VCC), U700.3 (VDD), U701.18 (VDD), U702.3 (VDD), U703.3 (VDD)
P8V: C105.1, D105.1 (K), D106.2 (A), J801.1, R505.2, REG101.3 (VO), U500.2 (VDD)
VBAT: C106.1, D500.1 (A), REG100.8 (OUT), U502.6 (VBAT)
VBUS: D505.2 (A), J501.A4 (VBUS), J501.A9 (VBUS), J501.B4 (VBUS), J501.B9 (VBUS)
VBUS2: D600.2 (A2), D604.2 (A), J601.A4 (VBUS), J601.A9 (VBUS), J601.B4 (VBUS), J601.B9 (VBUS), R602.1

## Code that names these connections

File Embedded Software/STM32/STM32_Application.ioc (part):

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Mcu.Name=STM32H750VBTx
Mcu.Package=LQFP100
Mcu.UserName=STM32H750VBTx
PA0.GPIOParameters=GPIO_Label
PA0.GPIO_Label=ESP32_RX
PA0.Mode=Asynchronous
PA0.Signal=UART4_TX
PA1.GPIOParameters=GPIO_Label
PA1.GPIO_Label=ESP32_TX
PA1.Mode=Asynchronous
PA1.Signal=UART4_RX
PA11.GPIOParameters=PinAttribute
PA11.Mode=Device_Only
PA11.PinAttribute=Free
PA11.Signal=USB_OTG_FS_DM
PA12.GPIOParameters=PinAttribute
PA12.Mode=Device_Only
PA12.PinAttribute=Free
PA12.Signal=USB_OTG_FS_DP
PA13\ (JTMS/SWDIO).Mode=Serial_Wire
PA13\ (JTMS/SWDIO).Signal=DEBUG_JTMS-SWDIO
PA14\ (JTCK/SWCLK).Mode=Serial_Wire
PA14\ (JTCK/SWCLK).Signal=DEBUG_JTCK-SWCLK
PA15\ (JTDI).GPIOParameters=PinAttribute
PA15\ (JTDI).Mode=Asynchronous
PA15\ (JTDI).PinAttribute=Free
PA15\ (JTDI).Signal=UART7_TX
PA4.GPIOParameters=GPIO_Label
PA4.GPIO_Label=Beep_Out
PA4.Signal=COMP_DAC11_group
PA6.GPIOParameters=GPIO_Label
PA6.GPIO_Label=LMOUT
PA6.Signal=ADCx_INP3
PA7.GPIOParameters=GPIO_Label,PinAttribute
PA7.GPIO_Label=illumination_in
PA7.PinAttribute=Free
PA7.Signal=S_TIM14_CH1
PA8.GPIOParameters=GPIO_Label,PinAttribute
PA8.GPIO_Label=OUT25MHz
PA8.Mode=Clock-out-1
PA8.PinAttribute=Free
PA8.Signal=RCC_MCO_1
PA9.GPIOParameters=PinAttribute
PA9.Mode=Activate_VBUS
PA9.PinAttribute=Free
PA9.Signal=USB_OTG_FS_VBUS
PB0.GPIOParameters=GPIO_Label,PinAttribute
PB0.GPIO_Label=CDEJECT
PB0.PinAttribute=Free
PB0.Signal=GPIO_Output
PB10.GPIOParameters=GPIO_Label
PB10.GPIO_Label=U1LCD_SCK
PB10.Mode=Full_Duplex_Master
PB10.Signal=SPI2_SCK
PB12.GPIOParameters=GPIO_Label
PB12.GPIO_Label=CAN2_RXD
PB12.Mode=FDCAN_Activate
PB12.Signal=FDCAN2_RX
PB13.GPIOParameters=GPIO_Label
PB13.GPIO_Label=CAN2_TXD
PB13.Mode=FDCAN_Activate
PB13.Signal=FDCAN2_TX
PB14.GPIOParameters=GPIO_Label
PB14.GPIO_Label=FAN_OUT
PB14.Signal=S_TIM12_CH1
PB2.GPIOParameters=GPIO_Label,PinAttribute
PB2.GPIO_Label=QSPI_CLK
PB2.Mode=Single Bank 1
PB2.PinAttribute=Free
PB2.Signal=QUADSPI_CLK
PB3\ (JTDO/TRACESWO).GPIOParameters=GPIO_Label,PinAttribute
PB3\ (JTDO/TRACESWO).GPIO_Label=Backlight_PWM
PB3\ (JTDO/TRACESWO).PinAttribute=Free
PB3\ (JTDO/TRACESWO).Signal=S_TIM2_CH2
PB6.GPIOParameters=GPIO_Label
PB6.GPIO_Label=QSPI_CS
PB6.Mode=Single Bank 1
PB6.Signal=QUADSPI_BK1_NCS
PB8.Mode=I2C
PB8.Signal=I2C1_SCL
PB9.Mode=I2C
PB9.Signal=I2C1_SDA
PC0.GPIOParameters=GPIO_Label
PC0.GPIO_Label=U1LCD_CS
PC0.Signal=GPIO_Output
PC1.GPIOParameters=GPIO_Label
PC1.GPIO_Label=U1LCD_MOSI
PC1.Mode=Full_Duplex_Master
PC1.Signal=SPI2_MOSI
PC10.GPIOParameters=GPIO_Label,PinAttribute
PC10.GPIO_Label=QSPI_D1
PC10.Mode=Single Bank 1
PC10.PinAttribute=Free
PC10.Signal=QUADSPI_BK1_IO1
PC12.GPIOParameters=GPIO_Label,PinAttribute
PC12.GPIO_Label=STM32_TX
PC12.Mode=Asynchronous
PC12.PinAttribute=Free
PC12.Signal=UART5_TX
PC13.GPIOParameters=GPIO_Label
PC13.GPIO_Label=OUT1Hz
PC13.Mode=Calibration_1Hz
PC13.Signal=RTC_OUT_CALIB
PC14-OSC32_IN\ (OSC32_IN).Mode=LSE-External-Oscillator
PC14-OSC32_IN\ (OSC32_IN).Signal=RCC_OSC32_IN
PC15-OSC32_OUT\ (OSC32_OUT).Mode=LSE-External-Oscillator
PC15-OSC32_OUT\ (OSC32_OUT).Signal=RCC_OSC32_OUT
PC2_C.GPIOParameters=GPIO_Label
PC2_C.GPIO_Label=U1LCD_MISO
PC2_C.Mode=Full_Duplex_Master
PC2_C.Signal=SPI2_MISO
PC3_C.GPIOParameters=GPIO_Label
PC3_C.GPIO_Label=WheelButtonIN
PC3_C.Signal=ADC3_INP1
PC4.GPIOParameters=GPIO_Label,PinAttribute
PC4.GPIO_Label=CD MUTE
PC4.PinAttribute=Free
PC4.Signal=GPIO_Output
PC5.GPIOParameters=GPIO_Label,PinAttribute
PC5.GPIO_Label=CDENABLE
PC5.PinAttribute=Free
PC5.Signal=GPIO_Output
PC6.GPIOParameters=GPIO_Label
PC6.GPIO_Label=CDBUS+
PC6.Signal=S_TIM3_CH1
PC9.GPIOParameters=GPIO_Label
PC9.GPIO_Label=QSPI_D0
PC9.Mode=Single Bank 1
PC9.Signal=QUADSPI_BK1_IO0
PD0.GPIOParameters=GPIO_Label,PinAttribute
PD0.GPIO_Label=CAN1_RXD
PD0.Mode=FDCAN_Activate
PD0.PinAttribute=Free
PD0.Signal=FDCAN1_RX
PD1.GPIOParameters=GPIO_Label,PinAttribute
PD1.GPIO_Label=CAN1_TXD
PD1.Mode=FDCAN_Activate
PD1.PinAttribute=Free
PD1.Signal=FDCAN1_TX
PD10.GPIOParameters=GPIO_Label
PD10.GPIO_Label=Temp_UP
PD10.Signal=GPIO_Output
PD11.GPIOParameters=GPIO_Label
PD11.GPIO_Label=Temp_DOWN
PD11.Signal=GPIO_Output
PD12.GPIOParameters=GPIO_Label
PD12.GPIO_Label=FAN_TACHO
PD12.Signal=S_TIM4_CH1
PD13.GPIOParameters=GPIO_Label
PD13.GPIO_Label=QSPI_D3
PD13.Mode=Single Bank 1
PD13.Signal=QUADSPI_BK1_IO3
PD2.GPIOParameters=GPIO_Label,PinAttribute
PD2.GPIO_Label=STM32_RX
PD2.Mode=Asynchronous
PD2.PinAttribute=Free
PD2.Signal=UART5_RX
PD4.GPIOParameters=GPIO_Label,PinAttribute
PD4.GPIO_Label=LCD_EN
PD4.PinAttribute=Free
PD4.Signal=GPIO_Output
PD5.GPIOParameters=GPIO_Label,PinAttribute
PD5.GPIO_Label=LCD_ACMODE
PD5.PinAttribute=Free
PD5.Signal=GPIO_Output
PD6.GPIOParameters=GPIO_Label,PinAttribute
PD6.GPIO_Label=LCD_RSMODE
PD6.PinAttribute=Free
PD6.Signal=GPIO_Output
PD8.Signal=GPIO_Output
PD9.GPIOParameters=GPIO_Label
PD9.GPIO_Label=Fan_DOWN
PD9.Signal=GPIO_Output
PE10.GPIOParameters=GPIO_Label
PE10.GPIO_Label=APSTATE
PE10.Signal=GPIO_Output
PE11.GPIOParameters=GPIO_Label
PE11.GPIO_Label=AMP_MUTE
PE11.Signal=GPIO_Output
PE12.GPIOParameters=GPIO_Label
PE12.GPIO_Label=AMPSTATE
PE12.Signal=GPIO_Output
PE13.GPIOParameters=GPIO_Label
PE13.GPIO_Label=Tuner_RST
PE13.Signal=GPIO_Output
PE2.GPIOParameters=GPIO_Label
PE2.GPIO_Label=QSPI_D2
PE2.Mode=Single Bank 1
PE2.Signal=QUADSPI_BK1_IO2
PE3.GPIOParameters=GPIO_Label
PE3.GPIO_Label=LED_1Hz
PE3.Signal=GPIO_Output
PE5.GPIOParameters=GPIO_Label
PE5.GPIO_Label=PWM_OUT
PE5.Signal=S_TIM15_CH1
PE7.Mode=Asynchronous
PE7.Signal=UART7_RX
PH0-OSC_IN\ (PH0).Mode=HSE-External-Oscillator
PH0-OSC_IN\ (PH0).Signal=RCC_OSC_IN
PH1-OSC_OUT\ (PH1).Mode=HSE-External-Oscillator
PH1-OSC_OUT\ (PH1).Signal=RCC_OSC_OUT
RCC.SYSCLKFreq_VALUE=400000000
RCC.SYSCLKSource=RCC_SYSCLKSOURCE_PLLCLK
board=custom

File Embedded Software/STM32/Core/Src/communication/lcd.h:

/*
 * lcd.h
 * Created on: 23 Mar 2026
 * Author: Bradley Port
 * Royal Holloway University of London
 * EE3000
 *
 * Driver for OEM RX-8 LCD display
 */

#ifndef COMMUNICATION_LCD_H_
#define COMMUNICATION_LCD_H_

#include "stm32h7xx_hal.h"
#include "main.h"
#include <string.h>

#define LCD_AC_PORT     GPIOD
#define LCD_AC_PIN      LCD_ACMODE_Pin

#define LCD_RS_PORT     GPIOD
#define LCD_RS_PIN      LCD_RSMODE_Pin

#define LCD_CS_PORT     GPIOC
#define LCD_CS_PIN      U1LCD_CS_Pin

#define LCD_PWM_TIMER       htim2
#define LCD_PWM_CHANNEL     TIM_CHANNEL_2
#define LCD_PWM_DUTY_75     ((uint32_t)(4294967295UL * 0.75f))

#define LCD_ICON_BASE   0x90
#define LCD_ICON_COUNT  14

void LCD_Init(SPI_HandleTypeDef *hspi, TIM_HandleTypeDef *htim);

static inline void DWT_Init(void)
{
    CoreDebug->DEMCR |= CoreDebug_DEMCR_TRCENA_Msk;
    DWT->CYCCNT = 0;
    DWT->CTRL  |= DWT_CTRL_CYCCNTENA_Msk;
}

static inline void DWT_Delay_us(uint32_t us)
{
    uint32_t start  = DWT->CYCCNT;
    uint32_t cycles = us * (SystemCoreClock / 1000000);
    while ((DWT->CYCCNT - start) < cycles);
}

// Core SPI
void LCD_SendCommand(uint8_t cmd);
void LCD_SendData(uint8_t data);
void LCD_SetICON(uint8_t address, uint8_t value);

// Display control
void LCD_Startup(void);
void LCD_Clear(void);
void LCD_Home(void);
void LCD_Reset(void);
void LCD_ResetIcons(void);
void LCD_Print(const char *text);

// Backlight
void LCD_SetBacklight(uint8_t percent);

// Content
void LCD_SetFanSpeed(uint8_t speed);
void LCD_SetVentMode(uint8_t mode);
void LCD_SetDivider();
void LCD_SetMinDigit(uint8_t digit, uint8_t value);
void LCD_SetSevenSegment(uint8_t col, uint8_t value);
void LCD_SetCircMode(uint8_t circ);
void LCD_SetAuto(uint8_t Auto);
void LCD_SetAC(uint8_t AC);
void LCD_SetECO(uint8_t eco);
void LCD_SetDemistFront(uint8_t demist);

void LCD_FlushIcons(void);
void LCD_FlushSevenSegment(void);
void LCD_SetMinute(uint8_t col, uint8_t value);
void LCD_SetHour(uint8_t col, uint8_t value);
void LCD_SetTempDigit(uint8_t col, uint8_t value);
void LCD_SetTime();
void LCD_SetTemperature(uint8_t tens, uint8_t units, uint8_t decimal);
void LCD_Test(void);

#endif /* COMMUNICATION_LCD_H_ */

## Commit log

2026-03-02 Added PCB V1 Files
2026-03-04 Add files via upload
    Bluetooth Music functionality added
2026-03-04 Add files via upload
    Added clock and date functionality. Small GUI changes, as well as enhanced bluetooth functions.
2026-03-07 More UART comms, Volume pop up now working.
2026-04-14 STM32 Software Upload
2026-05-12 Firmware V1.1
